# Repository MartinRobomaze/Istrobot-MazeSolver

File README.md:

# Istrobot-MazeSolver

## ESP32 PINOUT GUIDE
Before connecting anything to ESP32, check this link: https://randomnerdtutorials.com/esp32-pinout-reference-gpios/  
ESP32 has some piins which are not allowed to use because of integrated SPI flash(6-11), boot failing whe pulled high(12) and other strange things.
There are 2 more pins which are not allowed to use - pin 21 and 22 - these will be used for I2C distance sensors communication.  
**SENSOR_VP = GPIO36  
SENSOR_VN = GPIO39**

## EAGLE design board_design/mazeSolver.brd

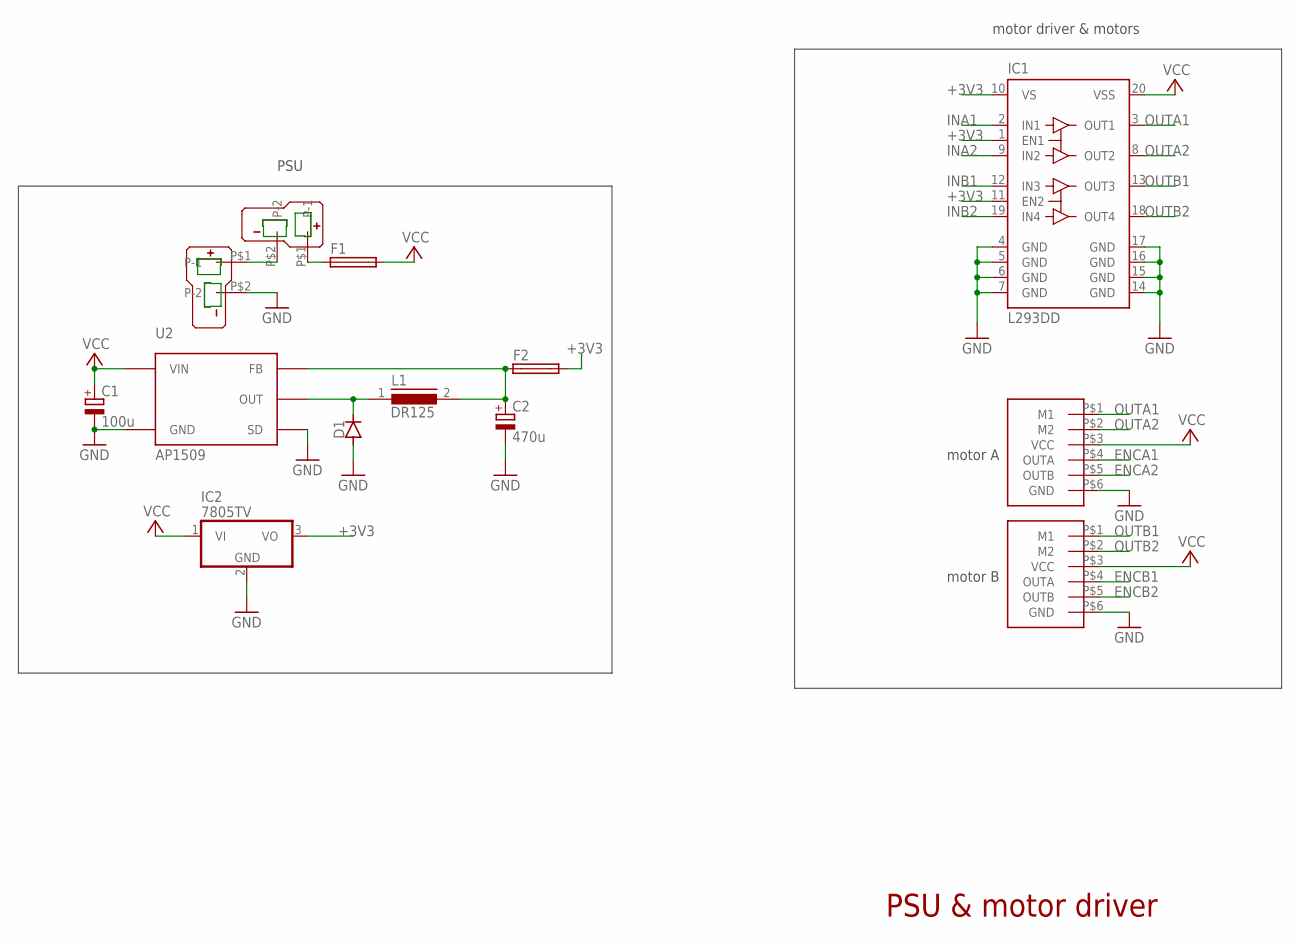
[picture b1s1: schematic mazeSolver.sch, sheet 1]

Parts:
C1: 100u; 140CLH-0810; MPN 100YXF100MEFC12.5X20
C2: 470u; 140CLH-0810
D1: DIODE-DO214AC; DO214AC
F1: 195591812; C1812K
F2: 195591206; C1206K
IC1: L293DD; SO20
IC2: 7805TV; TO220V
L1: DR125
U2: AP1509-SOP8L; SOP-8L
U$1, U$9: T-PLUG_CONNECTOR; T_PLUG_CONNECTOR
U$2, U$3: POLOLU_ENCODER

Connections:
+3V3: F2.2, IC1.1 (EN1), IC1.10 (VS), IC1.11 (EN2), IC2.3 (VO); also elsewhere on the board
ENCA1: U$2.P$4 (OUTA); also elsewhere on the board
ENCA2: U$2.P$5 (OUTB); also elsewhere on the board
ENCB1: U$3.P$4 (OUTA); also elsewhere on the board
ENCB2: U$3.P$5 (OUTB); also elsewhere on the board
GND: C1.-, C2.-, D1.A, IC1.4 (GND), IC1.5 (GND), IC1.6 (GND), IC1.7 (GND), IC1.14 (GND), IC1.15 (GND), IC1.16 (GND), IC1.17 (GND), IC2.2 (GND), U2.4 (SD), U2.5 (GND), U2.6 (GND), U2.7 (GND), U2.8 (GND), U$1.P$2 (P-2), U$2.P$6 (GND), U$3.P$6 (GND); also elsewhere on the board
INA1: IC1.2 (IN1); also elsewhere on the board
INA2: IC1.9 (IN2); also elsewhere on the board
INB1: IC1.12 (IN3); also elsewhere on the board
INB2: IC1.19 (IN4); also elsewhere on the board
unnamed: D1.C, L1.1, U2.2 (OUT)
unnamed: U$1.P$1 (P-1), U$9.P$2 (P-2)
unnamed: F1.1, U$9.P$1 (P-1)
unnamed: C2.+, F2.1, L1.2, U2.3 (FB)
OUTA1: IC1.3 (OUT1), U$2.P$1 (M1)
OUTA2: IC1.8 (OUT2), U$2.P$2 (M2)
OUTB1: IC1.13 (OUT3), U$3.P$1 (M1)
OUTB2: IC1.18 (OUT4), U$3.P$2 (M2)
VCC: C1.+, F1.2, IC1.20 (VSS), IC2.1 (VI), U2.1 (VIN), U$2.P$3 (VCC), U$3.P$3 (VCC)

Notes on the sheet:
motor A
motor B
motor driver & motors
PSU & motor driver
PSU

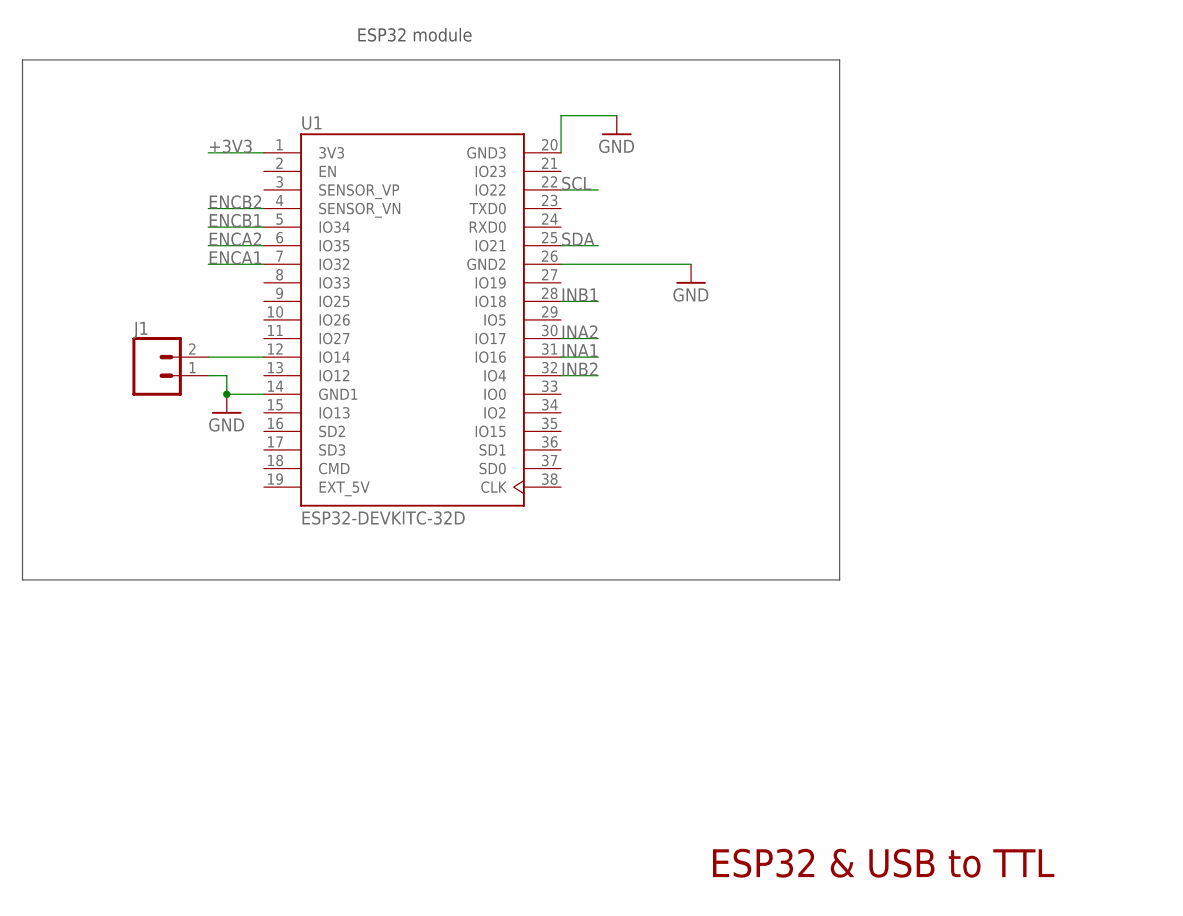
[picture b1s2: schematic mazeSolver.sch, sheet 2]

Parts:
J1: CONN_02; 1X02
U1: ESP32-DEVKITC-32D; MODULE_ESP32-DEVKITC-32D

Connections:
+3V3: U1.1 (3V3); also elsewhere on the board
ENCA1: U1.7 (IO32); also elsewhere on the board
ENCA2: U1.6 (IO35); also elsewhere on the board
ENCB1: U1.5 (IO34); also elsewhere on the board
ENCB2: U1.4 (SENSOR_VN); also elsewhere on the board
EXT_5V: U1.19 (EXT_5V)
GND: J1.1, U1.14 (GND1), U1.20 (GND3), U1.26 (GND2); also elsewhere on the board
INA1: U1.31 (IO16); also elsewhere on the board
INA2: U1.30 (IO17); also elsewhere on the board
INB1: U1.28 (IO18); also elsewhere on the board
INB2: U1.32 (IO4); also elsewhere on the board
unnamed: J1.2, U1.12 (IO14)
SCL: U1.22 (IO22); also elsewhere on the board
SDA: U1.25 (IO21); also elsewhere on the board

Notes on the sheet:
ESP32 & USB to TTL
ESP32 module

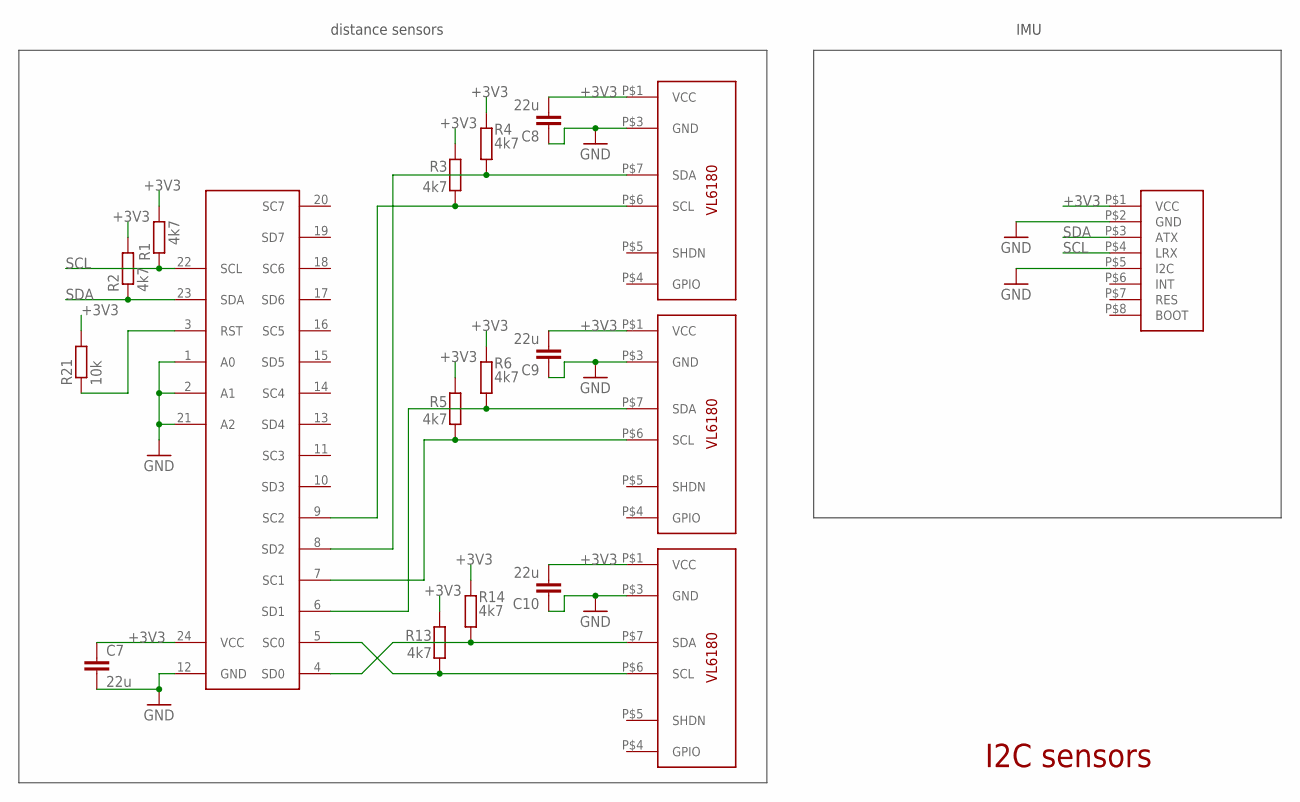
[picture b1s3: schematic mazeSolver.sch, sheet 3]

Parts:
C7, C8, C9, C10: 22u; C1206
R1, R2, R3, R4, R5, R6, R13, R14: 4k7; R1206
R21: 10k; R1206
U$4: TDA9548; SOIC24L
U$5, U$6, U$7: VL6180X
U$8: BNO055

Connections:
+3V3: C7.1, C8.1, C9.1, C10.1, R1.2, R2.2, R3.2, R4.2, R5.2, R6.2, R13.2, R14.2, R21.2, U$4.24 (VCC), U$5.P$1 (VCC), U$6.P$1 (VCC), U$7.P$1 (VCC), U$8.P$1 (VCC); also elsewhere on the board
GND: C7.2, C8.2, C9.2, C10.2, U$4.1 (A0), U$4.2 (A1), U$4.12 (GND), U$4.21 (A2), U$5.P$3 (GND), U$6.P$3 (GND), U$7.P$3 (GND), U$8.P$2 (GND), U$8.P$5 (I2C); also elsewhere on the board
unnamed: R13.1, U$4.5 (SC0), U$7.P$6 (SCL)
unnamed: R14.1, U$4.4 (SD0), U$7.P$7 (SDA)
unnamed: R6.1, U$4.6 (SD1), U$6.P$7 (SDA)
unnamed: R5.1, U$4.7 (SC1), U$6.P$6 (SCL)
unnamed: R4.1, U$4.8 (SD2), U$5.P$7 (SDA)
unnamed: R3.1, U$4.9 (SC2), U$5.P$6 (SCL)
unnamed: R21.1, U$4.3 (RST)
SCL: R1.1, U$4.22 (SCL), U$8.P$4 (LRX); also elsewhere on the board
SDA: R2.1, U$4.23 (SDA), U$8.P$3 (ATX); also elsewhere on the board

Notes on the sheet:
I2C sensors
distance sensors
IMU

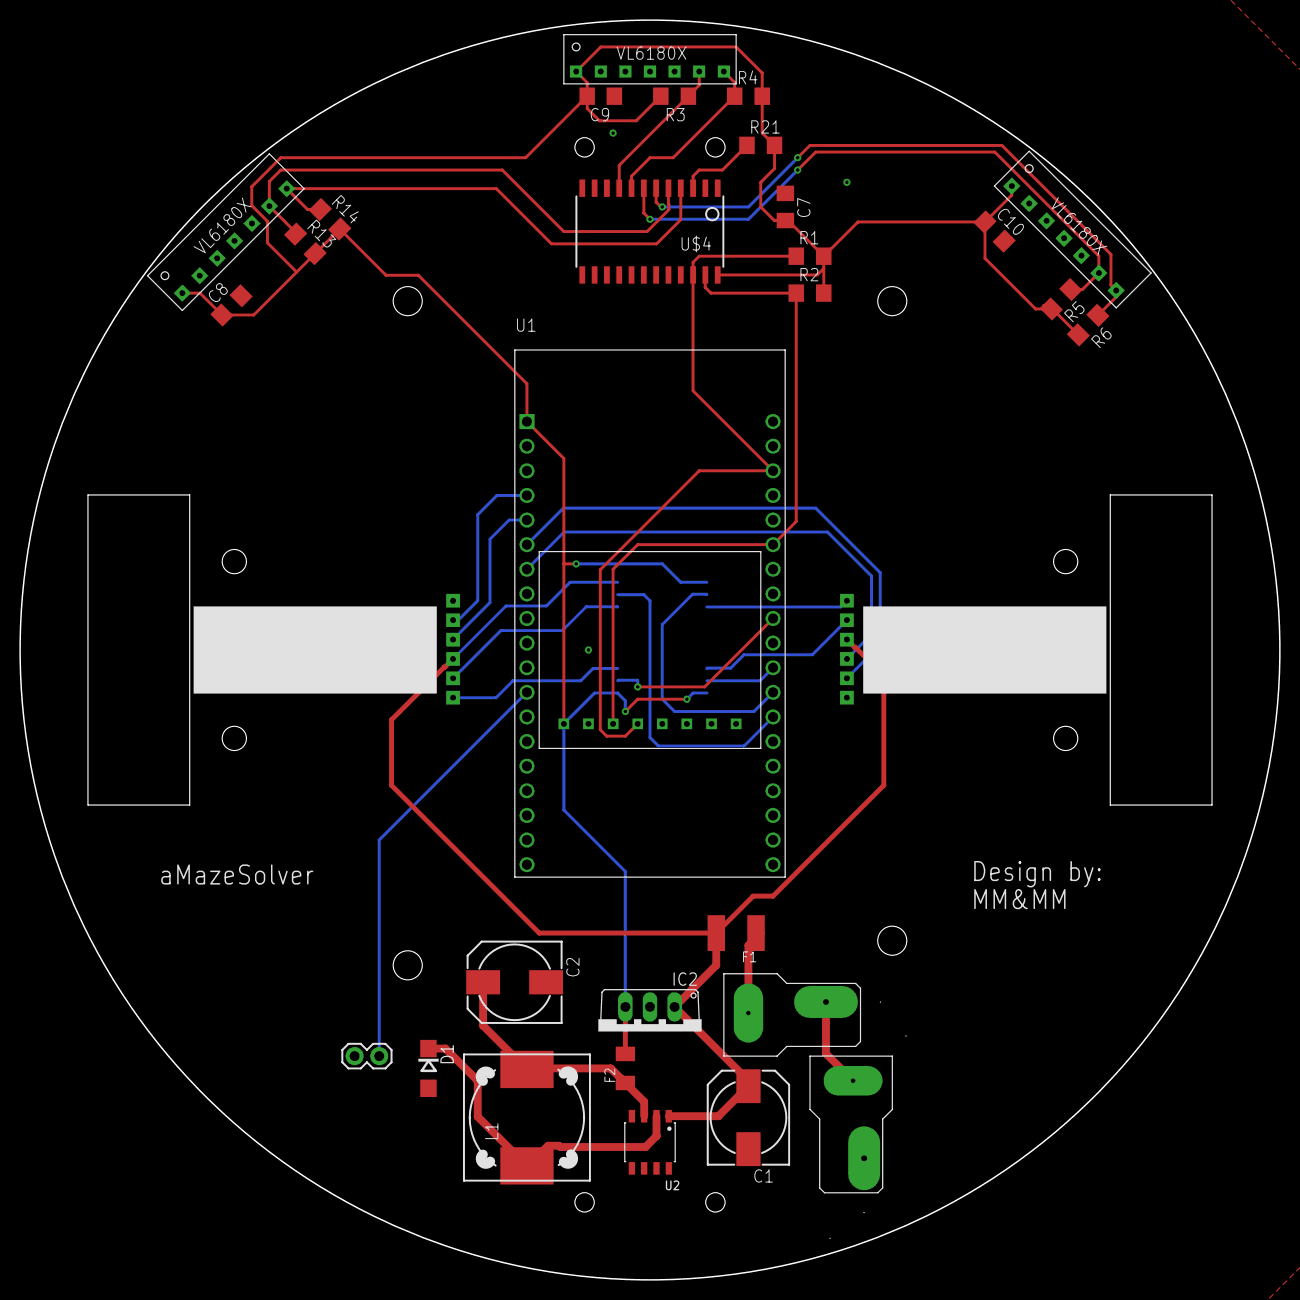
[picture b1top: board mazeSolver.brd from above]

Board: 2 copper layers, 130.0 x 130.0 mm, 33 parts (1 on the bottom side), 29 nets.

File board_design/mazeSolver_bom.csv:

"Part";"Value";"Device";"Package";"Description";"AVAILABILITY";"DESCRIPTION";"MF";"MP";"MPN";"OC_FARNELL";"PACKAGE";"POPULARITY";"PRICE";"PURCHASE-URL";"SPICEPREFIX";
"C1";"100u";"CPOL-EU140CLH-0810";"140CLH-0810";"POLARIZED CAPACITOR, European symbol";"";"";"RUBYCON";"";"100YXF100MEFC12.5X20";"1144642";"";"4";"";"";"C";
"C2";"470u";"CPOL-EU140CLH-0810";"140CLH-0810";"POLARIZED CAPACITOR, European symbol";"";"";"";"";"";"unknown";"";"4";"";"";"C";
"C7";"22u";"C-EUC1206";"C1206";"CAPACITOR, European symbol";"";"";"";"";"";"unknown";"";"54";"";"";"C";
"C8";"22u";"C-EUC1206";"C1206";"CAPACITOR, European symbol";"";"";"";"";"";"unknown";"";"54";"";"";"C";
"C9";"22u";"C-EUC1206";"C1206";"CAPACITOR, European symbol";"";"";"";"";"";"unknown";"";"54";"";"";"C";
"C10";"22u";"C-EUC1206";"C1206";"CAPACITOR, European symbol";"";"";"";"";"";"unknown";"";"54";"";"";"C";
"D1";"";"DIODE-DO214AC";"DO214AC";"DIODE";"";"";"";"";"";"unknown";"";"14";"";"";"";
"F1";"";"195591812";"C1812K";"FUSE HOLDER";"";"";"";"";"";"";"";"";"";"";"";
"F2";"";"195591206";"C1206K";"FUSE HOLDER";"";"";"";"";"";"";"";"";"";"";"";
"IC1";"L293DD";"L293DD";"SO20";"PUSH-PULL FOUR CHANNEL DRIVER WITH DIODES";"";"";"";"";"";"unknown";"";"2";"";"";"";
"IC2";"7805TV";"7805TV";"TO220V";"Positive VOLTAGE REGULATOR";"";"";"";"";"";"unknown";"";"57";"";"";"";
"J1";"";"CONN_02";"1X02";"Multi connection point. Often used as Generic Header-pin footprint for 0.1 inch spaced/style header connections";"";"";"";"";"";"unknown";"";"";"";"";"";
"L1";"DR125";"DR125";"DR125";"High Power Density, High Efficiency, Shielded Inductors";"";"";"";"";"";"unknown";"";"1";"";"";"L";
"R1";"4k7";"R-EU_R1206";"R1206";"RESISTOR, European symbol";"";"";"";"";"";"unknown";"";"41";"";"";"R";
"R2";"4k7";"R-EU_R1206";"R1206";"RESISTOR, European symbol";"";"";"";"";"";"unknown";"";"41";"";"";"R";
"R3";"4k7";"R-EU_R1206";"R1206";"RESISTOR, European symbol";"";"";"";"";"";"unknown";"";"41";"";"";"R";
"R4";"4k7";"R-EU_R1206";"R1206";"RESISTOR, European symbol";"";"";"";"";"";"unknown";"";"41";"";"";"R";
"R5";"4k7";"R-EU_R1206";"R1206";"RESISTOR, European symbol";"";"";"";"";"";"unknown";"";"41";"";"";"R";
"R6";"4k7";"R-EU_R1206";"R1206";"RESISTOR, European symbol";"";"";"";"";"";"unknown";"";"41";"";"";"R";
"R13";"4k7";"R-EU_R1206";"R1206";"RESISTOR, European symbol";"";"";"";"";"";"unknown";"";"41";"";"";"R";
"R14";"4k7";"R-EU_R1206";"R1206";"RESISTOR, European symbol";"";"";"";"";"";"unknown";"";"41";"";"";"R";
"R21";"10k";"R-EU_R1206";"R1206";"RESISTOR, European symbol";"";"";"";"";"";"unknown";"";"41";"";"";"R";
"U$1";"T-PLUG_CONNECTOR";"T-PLUG_CONNECTOR";"T_PLUG_CONNECTOR";"";"";"";"";"";"";"unknown";"";"";"";"";"";
"U$2";"POLOLU_ENCODER";"POLOLU_ENCODER";"POLOLU_ENCODER";"";"";"";"";"";"";"";"";"";"";"";"";
"U$3";"POLOLU_ENCODER";"POLOLU_ENCODER";"POLOLU_ENCODER";"";"";"";"";"";"";"unknown";"";"";"";"";"";
"U$4";"TDA9548";"TDA9548";"SOIC24L";"";"";"";"";"";"";"unknown";"";"";"";"";"";
"U$5";"VL6180X";"VL6180X";"VL6180X";"";"";"";"";"";"";"unknown";"";"";"";"";"";
"U$6";"VL6180X";"VL6180X";"VL6180X";"";"";"";"";"";"";"unknown";"";"";"";"";"";
"U$7";"VL6180X";"VL6180X";"VL6180X";"";"";"";"";"";"";"unknown";"";"";"";"";"";
"U$8";"BNO055";"BNO055";"BNO055";"";"";"";"";"";"";"";"";"";"";"";"";
"U$9";"T-PLUG_CONNECTOR";"T-PLUG_CONNECTOR";"T_PLUG_CONNECTOR";"";"";"";"";"";"";"unknown";"";"";"";"";"";
"U1";"ESP32-DEVKITC-32D";"ESP32-DEVKITC-32D";"MODULE_ESP32-DEVKITC-32D";"Eval Board For Esp-Wroom-32 Check prices";"Warning";" EVAL BOARD FOR ESP-WROOM-32 ";"Espressif Systems";"ESP32-DEVKITC-32D";"";"";"None";"";"None";"https://pricing.snapeda.com/search/part/ESP32-DEVKITC-32D/?ref=eda";"";
"U2";"AP1509-SOP8L";"AP1509-SOP8L";"SOP-8L";"AP1509";"";"";"";"";"";"unknown";"";"";"";"";"";

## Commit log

2020-10-16 PSU and motors drivers
2020-10-16 USB and reset circuitry.
2020-10-23 Finished schematic
2020-10-25 ESP32 circuit reworked.
2020-11-03 Final changes.
2020-11-03 feature-4 | Schematic design for mazeSolver (#5)
2020-11-04 Components placement
2020-11-04 Routing
2020-11-05 Added mounting holes
2020-11-07 PCB Design
2020-11-07 DRC Checks are passing
2020-11-11 Added two 3d packages
2020-11-12 A lot of changes
2020-11-13 PR review changes
2021-02-08 Board design changes
2021-02-08 Added bom and gerbers

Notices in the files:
parts and their libraries:
SparkFun-Connectors: Licensing: Creative Commons ShareAlike 4.0 International - https://creativecommons.org/licenses/by-sa/4.0
